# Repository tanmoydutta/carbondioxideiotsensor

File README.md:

Cyllene is an IoT module for Carbon di Oxide concentration detection. It is based on SCD-41 CO2 sensor from Sensirion. The core controller is an ESP32 D4 Pico for WiFi and Bluetooth/BLE connectivity. Features include - 
- Carbon-di-Oxide sensor
- WiFi and Bluetooth/BLE connectivity
- Onboard antenna
- Programmable using onboard USB UART interface
- USB Type C connector
- USB / LiPo Battery powered (Optional)
- Onboard LiPo charger (Optional)

This is a conceptual view of the new enclosure for mounting on a whiteboard -

This project is certified for Open Source Hardware:
<p align="center">
  
</p>

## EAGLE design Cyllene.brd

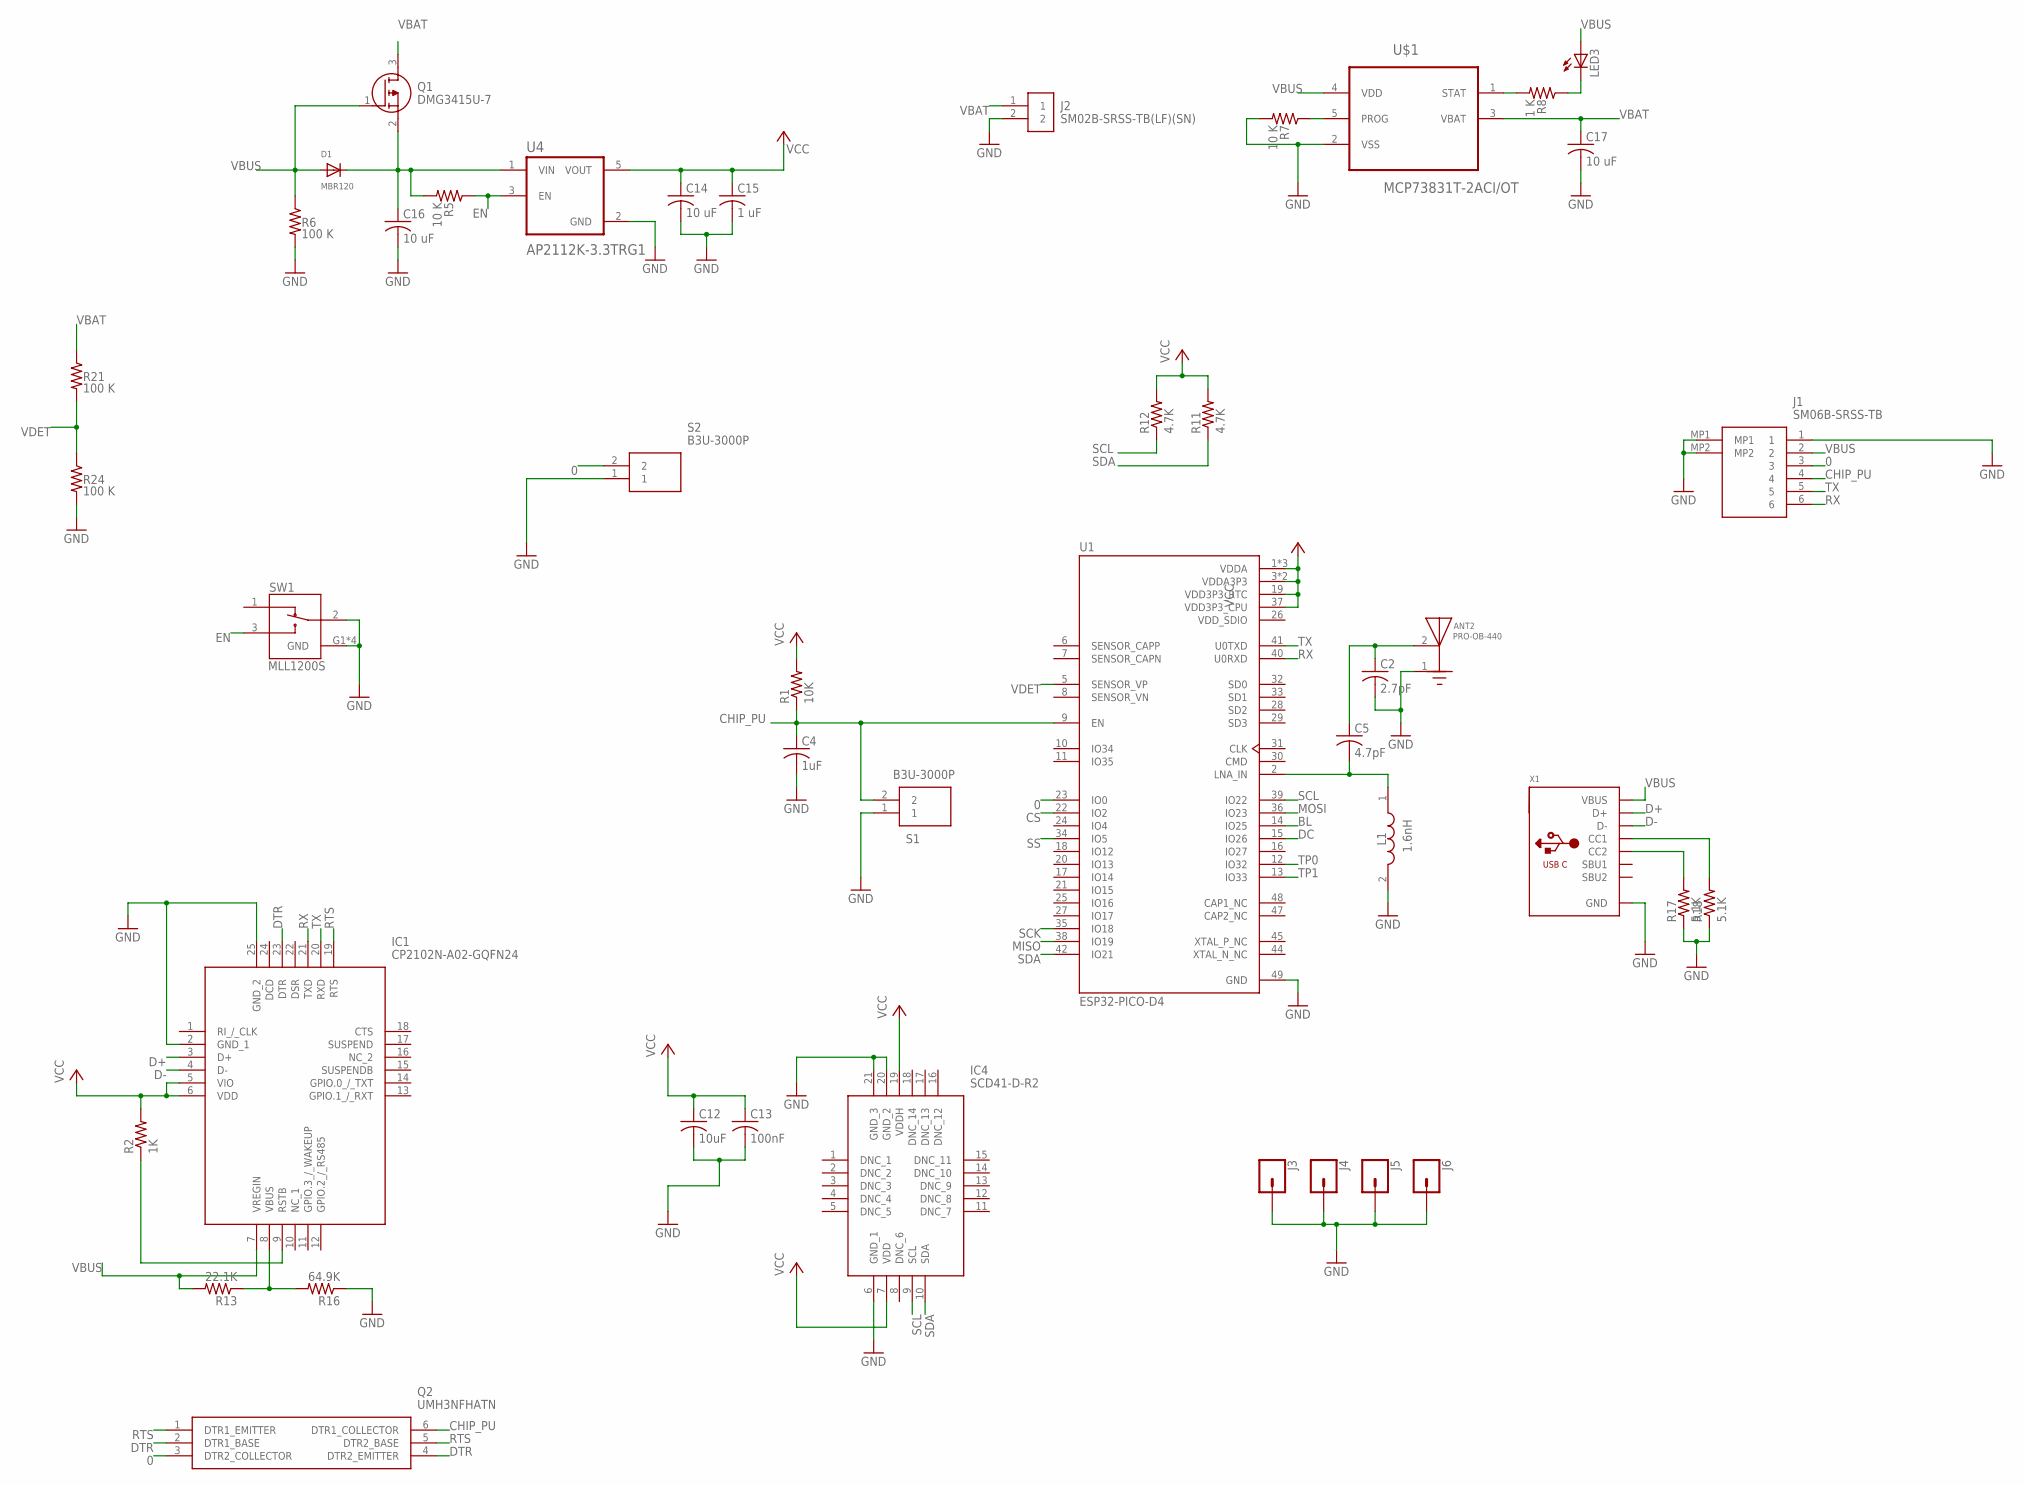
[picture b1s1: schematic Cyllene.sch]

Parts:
ANT2: PRO-OB-440; ANT_PRO-OB-440
C2: 2.7pF; C0402
C4: 1uF; C0402
C5: 4.7pF; C0402
C12: 10uF; C0402
C13: 100nF; C0402
C14, C16, C17: 10 uF; C0402
C15: 1 uF; C0402
D1: MBR120; SOD-123
IC1: CP2102N-A02-GQFN24; QFN50P400X400X80-25N
IC4: SCD41-D-R2; SCD41DR2
J1: SM06B-SRSS-TB; SM06BSRSSTB
J2: SM02B-SRSS-TB(LF)(SN)
J3, J4, J5, J6: CONN_01PTH_2MM; 1X01_2MM
L1: 1.6nH; LQW15CNR20J00B
LED3: LEDCHIPLED_0603; CHIPLED_0603
Q1: DMG3415U-7; SOT96P240X100-3N
Q2: UMH3NFHATN; SOT65P210X100-6N
R1: 10K; R0402
R2: 1K; R0402
R5, R7: 10 K; R0402
R6, R21, R24: 100 K; R0402
R8: 1 K; R0402
R11, R12: 4.7K; R0402
R13: 22.1K; R0402
R16: 64.9K; R0402
R17, R18: 5.1K; R0402
S1, S2: B3U-3000P; B3U-1000P
SW1: MLL1200S; SW_MLL1200S
U1: ESP32-PICO-D4; PQFN50P700X700X104-49N
U4: AP2112K-3.3TRG1; SOT95P285X140-5N
U$1: MCP73831T-2ACI/OT; SOT95P280X145-5N
X1: MICROBUILDER_USB_C; MICROBUILDER_USB_C_CUSB31-CFM2AX-01-X

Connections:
0: J1.3, Q2.3 (DTR2_COLLECTOR), S2.2, U1.23 (IO0)
BL: U1.14 (IO25)
CHIP_PU: C4.1, J1.4, Q2.6 (DTR1_COLLECTOR), R1.1, S1.2, U1.9 (EN)
CS: U1.22 (IO2)
D+: IC1.3 (D+), X1.A6 (D+), X1.B6 (D+)
D-: IC1.4 (D-), X1.A7 (D-), X1.B7 (D-)
DC: U1.15 (IO26)
DTR: IC1.23 (DTR), Q2.2 (DTR1_BASE), Q2.4 (DTR2_EMITTER)
EN: R5.1, SW1.3, U4.3 (EN)
GND: ANT2.1 (GND), C2.2, C4.2, C12.2, C13.2, C14.2, C15.2, C16.2, C17.2, IC1.2 (GND_1), IC1.25 (GND_2), IC4.6 (GND_1), IC4.20 (GND_2), IC4.21 (GND_3), J1.1, J1.MP1, J1.MP2, J2.2, J3.1, J4.1, J5.1, J6.1, L1.2, R6.2, R7.2, R16.1, R17.1, R18.1, R24.2, S1.1, S2.1, SW1.2, SW1.G1 (GND), SW1.G2 (GND), SW1.G3 (GND), SW1.G4 (GND), U1.49 (GND), U4.2 (GND), U$1.2 (VSS), X1.A1B12 (GND), X1.B1A12 (GND)
MISO: U1.38 (IO19)
MOSI: U1.36 (IO23)
unnamed: C5.2, L1.1, U1.2 (LNA_IN)
unnamed: ANT2.2 (FEED), C2.1, C5.1
unnamed: C16.1, D1.C, Q1.2 (S), R5.2, U4.1 (VIN)
unnamed: IC1.9 (RSTB), R2.1
unnamed: IC1.8 (VBUS), R13.1, R16.2
unnamed: R18.2, X1.A5 (CC1)
unnamed: R17.2, X1.B5 (CC2)
unnamed: R8.2, U$1.1 (STAT)
unnamed: R7.1, U$1.5 (PROG)
unnamed: LED3.C, R8.1
RTS: IC1.19 (RTS), Q2.1 (DTR1_EMITTER), Q2.5 (DTR2_BASE)
RX: IC1.21 (TXD), J1.6, U1.40 (U0RXD)
SCK: U1.35 (IO18)
SCL: IC4.9 (SCL), R12.1, U1.39 (IO22)
SDA: IC4.10 (SDA), R11.1, U1.42 (IO21)
SS: U1.34 (IO5)
TP0: U1.12 (IO32)
TP1: U1.13 (IO33)
TX: IC1.20 (RXD), J1.5, U1.41 (U0TXD)
VBAT: C17.1, J2.1, Q1.3 (D), R21.1, U$1.3 (VBAT)
VBUS: D1.A, IC1.7 (VREGIN), J1.2, LED3.A, Q1.1 (G), R6.1, R13.2, U$1.4 (VDD), X1.A4B9 (VBUS), X1.B4A9 (VBUS)
VCC: C12.1, C13.1, C14.1, C15.1, IC1.5 (VIO), IC1.6 (VDD), IC4.7 (VDD), IC4.19 (VDDH), R1.2, R2.2, R11.2, R12.2, U1.1 (VDDA), U1.3 (VDDA3P3), U1.4 (VDDA3P3), U1.19 (VDD3P3_RTC), U1.37 (VDD3P3_CPU), U1.43 (VDDA), U1.46 (VDDA), U4.5 (VOUT)
VDD_SDIO: U1.26 (VDD_SDIO)
VDET: R21.2, R24.1, U1.5 (SENSOR_VP)

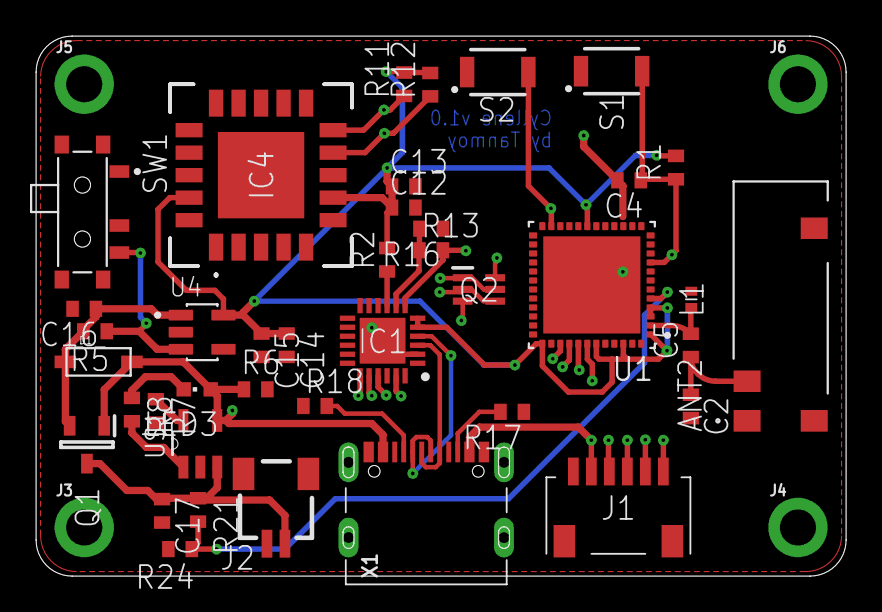
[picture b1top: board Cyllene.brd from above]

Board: 4 copper layers, 45.0 x 30.0 mm, 44 parts (0 on the bottom side), 26 nets.

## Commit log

2022-02-06 Eagle CAD files for sensors
2022-02-06 Initial description
2022-02-06 Sensor
2022-02-06 Adding image
2022-02-07 Update to documentation
2022-02-12 Update readme with license information
2026-01-07 Restructuring and enriching the content of this repo
2026-01-07 Update image links and add certification section
    Updated image links and added certification information.
2026-01-07 Modify OSHWA certification section in README
    Updated OSHWA certification image and link in README.
2026-01-08 Revise README for Cyllene IoT module details
    Updated the description of the Cyllene IoT module and made features optional. Added conceptual images for the new enclosure.

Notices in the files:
parts and their libraries:
SparkFun-Connectors: Licensing: Creative Commons ShareAlike 4.0 International - https://creativecommons.org/licenses/by-sa/4.0
